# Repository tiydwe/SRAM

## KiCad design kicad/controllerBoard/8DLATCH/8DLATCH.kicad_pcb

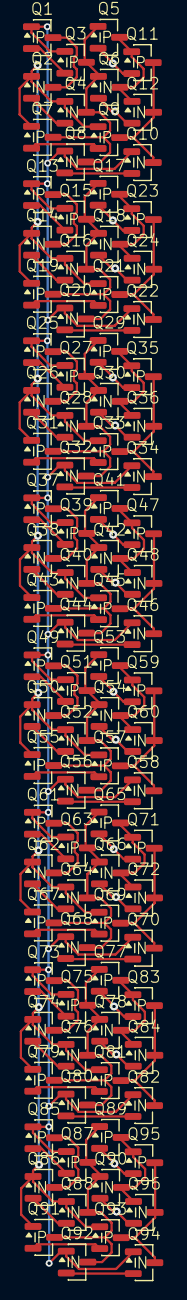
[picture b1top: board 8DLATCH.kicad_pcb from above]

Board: 2 copper layers, 96 parts (0 on the bottom side), 82 nets.

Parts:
Q1, Q3, Q5, Q7, Q9, Q11, Q13, Q15, Q17, Q19, Q21, Q23, Q25, Q27, Q29, Q31, Q33, Q35, Q37, Q39, Q41, Q43, Q45, Q47, Q49, Q51, Q53, Q55, Q57, Q59, Q61, Q63, Q65, Q67, Q69, Q71, Q73, Q75, Q77, Q79, Q81, Q83, Q85, Q87, Q89, Q91, Q93, Q95: Q_PMOS_GSD; SOT-23-P
Q2, Q4, Q6, Q8, Q10, Q12, Q14, Q16, Q18, Q20, Q22, Q24, Q26, Q28, Q30, Q32, Q34, Q36, Q38, Q40, Q42, Q44, Q46, Q48, Q50, Q52, Q54, Q56, Q58, Q60, Q62, Q64, Q66, Q68, Q70, Q72, Q74, Q76, Q78, Q80, Q82, Q84, Q86, Q88, Q90, Q92, Q94, Q96: Q_NMOS_GSD; SOT-23-N

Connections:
/D_{0}: Q1.3 (D), Q2.3 (D)
/D_{1}: Q13.3 (D), Q14.3 (D)
/D_{2}: Q25.3 (D), Q26.3 (D)
/D_{3}: Q37.3 (D), Q38.3 (D)
/D_{4}: Q49.3 (D), Q50.3 (D)
/D_{5}: Q61.3 (D), Q62.3 (D)
/D_{6}: Q73.3 (D), Q74.3 (D)
/D_{7}: Q85.3 (D), Q86.3 (D)
/EN: Q2.1 (G), Q4.1 (G), Q7.1 (G), Q9.1 (G), Q14.1 (G), Q16.1 (G), Q19.1 (G), Q21.1 (G), Q26.1 (G), Q28.1 (G), Q31.1 (G), Q33.1 (G), Q38.1 (G), Q40.1 (G), Q43.1 (G), Q45.1 (G), Q50.1 (G), Q52.1 (G), Q55.1 (G), Q57.1 (G), Q62.1 (G), Q64.1 (G), Q67.1 (G), Q69.1 (G), Q74.1 (G), Q76.1 (G), Q79.1 (G), Q81.1 (G), Q86.1 (G), Q88.1 (G), Q91.1 (G), Q93.1 (G)
/Q_{0}: Q9.3 (D), Q10.3 (D), Q11.3 (D), Q12.3 (D)
/Q_{1}: Q21.3 (D), Q22.3 (D), Q23.3 (D), Q24.3 (D)
/Q_{2}: Q33.3 (D), Q34.3 (D), Q35.3 (D), Q36.3 (D)
/Q_{3}: Q45.3 (D), Q46.3 (D), Q47.3 (D), Q48.3 (D)
/Q_{4}: Q57.3 (D), Q58.3 (D), Q59.3 (D), Q60.3 (D)
/Q_{5}: Q69.3 (D), Q70.3 (D), Q71.3 (D), Q72.3 (D)
/Q_{6}: Q81.3 (D), Q82.3 (D), Q83.3 (D), Q84.3 (D)
/Q_{7}: Q93.3 (D), Q94.3 (D), Q95.3 (D), Q96.3 (D)
/~EN: Q1.1 (G), Q3.1 (G), Q8.1 (G), Q10.1 (G), Q13.1 (G), Q15.1 (G), Q20.1 (G), Q22.1 (G), Q25.1 (G), Q27.1 (G), Q32.1 (G), Q34.1 (G), Q37.1 (G), Q39.1 (G), Q44.1 (G), Q46.1 (G), Q49.1 (G), Q51.1 (G), Q56.1 (G), Q58.1 (G), Q61.1 (G), Q63.1 (G), Q68.1 (G), Q70.1 (G), Q73.1 (G), Q75.1 (G), Q80.1 (G), Q82.1 (G), Q85.1 (G), Q87.1 (G), Q92.1 (G), Q94.1 (G)
/~Q_{0}: Q5.3 (D), Q6.3 (D), Q11.1 (G), Q12.1 (G)
/~Q_{1}: Q17.3 (D), Q18.3 (D), Q23.1 (G), Q24.1 (G)
/~Q_{2}: Q29.3 (D), Q30.3 (D), Q35.1 (G), Q36.1 (G)
/~Q_{3}: Q41.3 (D), Q42.3 (D), Q47.1 (G), Q48.1 (G)
/~Q_{4}: Q53.3 (D), Q54.3 (D), Q59.1 (G), Q60.1 (G)
/~Q_{5}: Q65.3 (D), Q66.3 (D), Q71.1 (G), Q72.1 (G)
/~Q_{6}: Q77.3 (D), Q78.3 (D), Q83.1 (G), Q84.1 (G)
/~Q_{7}: Q89.3 (D), Q90.3 (D), Q95.1 (G), Q96.1 (G)
unnamed: Q1.2 (S), Q3.2 (S)
unnamed: Q2.2 (S), Q4.2 (S)
unnamed: Q3.3 (D), Q4.3 (D), Q5.1 (G), Q6.1 (G), Q7.3 (D), Q8.3 (D)
unnamed: Q7.2 (S), Q9.2 (S)
unnamed: Q8.2 (S), Q10.2 (S)
unnamed: Q5.2 (S), Q11.2 (S)
unnamed: Q6.2 (S), Q12.2 (S)
unnamed: Q13.2 (S), Q15.2 (S)
unnamed: Q14.2 (S), Q16.2 (S)
unnamed: Q15.3 (D), Q16.3 (D), Q17.1 (G), Q18.1 (G), Q19.3 (D), Q20.3 (D)
unnamed: Q17.2 (S), Q23.2 (S)
unnamed: Q18.2 (S), Q24.2 (S)
unnamed: Q19.2 (S), Q21.2 (S)
unnamed: Q20.2 (S), Q22.2 (S)
unnamed: Q25.2 (S), Q27.2 (S)
unnamed: Q26.2 (S), Q28.2 (S)
unnamed: Q27.3 (D), Q28.3 (D), Q29.1 (G), Q30.1 (G), Q31.3 (D), Q32.3 (D)
unnamed: Q29.2 (S), Q35.2 (S)
unnamed: Q30.2 (S), Q36.2 (S)
unnamed: Q31.2 (S), Q33.2 (S)
unnamed: Q32.2 (S), Q34.2 (S)
unnamed: Q37.2 (S), Q39.2 (S)
unnamed: Q38.2 (S), Q40.2 (S)
unnamed: Q39.3 (D), Q40.3 (D), Q41.1 (G), Q42.1 (G), Q43.3 (D), Q44.3 (D)
unnamed: Q41.2 (S), Q47.2 (S)
unnamed: Q42.2 (S), Q48.2 (S)
unnamed: Q43.2 (S), Q45.2 (S)
unnamed: Q44.2 (S), Q46.2 (S)
unnamed: Q49.2 (S), Q51.2 (S)
unnamed: Q50.2 (S), Q52.2 (S)
unnamed: Q51.3 (D), Q52.3 (D), Q53.1 (G), Q54.1 (G), Q55.3 (D), Q56.3 (D)
unnamed: Q53.2 (S), Q59.2 (S)
unnamed: Q54.2 (S), Q60.2 (S)
unnamed: Q55.2 (S), Q57.2 (S)
unnamed: Q56.2 (S), Q58.2 (S)
unnamed: Q61.2 (S), Q63.2 (S)
unnamed: Q62.2 (S), Q64.2 (S)
unnamed: Q63.3 (D), Q64.3 (D), Q65.1 (G), Q66.1 (G), Q67.3 (D), Q68.3 (D)
unnamed: Q65.2 (S), Q71.2 (S)
unnamed: Q66.2 (S), Q72.2 (S)
unnamed: Q67.2 (S), Q69.2 (S)
unnamed: Q68.2 (S), Q70.2 (S)
unnamed: Q73.2 (S), Q75.2 (S)
unnamed: Q74.2 (S), Q76.2 (S)
unnamed: Q75.3 (D), Q76.3 (D), Q77.1 (G), Q78.1 (G), Q79.3 (D), Q80.3 (D)
unnamed: Q77.2 (S), Q83.2 (S)
unnamed: Q78.2 (S), Q84.2 (S)
unnamed: Q79.2 (S), Q81.2 (S)
unnamed: Q80.2 (S), Q82.2 (S)
unnamed: Q85.2 (S), Q87.2 (S)
unnamed: Q86.2 (S), Q88.2 (S)
unnamed: Q87.3 (D), Q88.3 (D), Q89.1 (G), Q90.1 (G), Q91.3 (D), Q92.3 (D)
unnamed: Q89.2 (S), Q95.2 (S)
unnamed: Q90.2 (S), Q96.2 (S)
unnamed: Q91.2 (S), Q93.2 (S)
unnamed: Q92.2 (S), Q94.2 (S)

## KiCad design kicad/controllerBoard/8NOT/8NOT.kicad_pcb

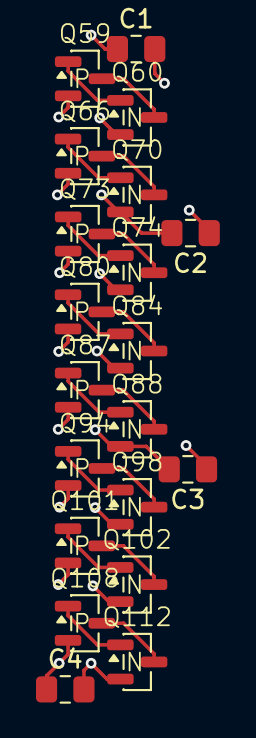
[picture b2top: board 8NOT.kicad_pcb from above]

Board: 2 copper layers, 20 parts (0 on the bottom side), 18 nets.

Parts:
C1, C2, C3, C4: C; C_0805_2012Metric_Pad1.18x1.45mm_HandSolder
Q59, Q66, Q73, Q80, Q87, Q94, Q101, Q108: Q_PMOS_GSD; SOT-23-P
Q60, Q70, Q74, Q84, Q88, Q98, Q102, Q112: Q_NMOS_GSD; SOT-23-N

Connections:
+5V: C1.1, C2.1, C3.1, C4.1, Q59.2 (S), Q66.2 (S), Q73.2 (S), Q80.2 (S), Q87.2 (S), Q94.2 (S), Q101.2 (S), Q108.2 (S)
/A_{0}: Q59.1 (G), Q60.1 (G)
/A_{1}: Q66.1 (G), Q70.1 (G)
/A_{2}: Q73.1 (G), Q74.1 (G)
/A_{3}: Q80.1 (G), Q84.1 (G)
/A_{4}: Q87.1 (G), Q88.1 (G)
/A_{5}: Q94.1 (G), Q98.1 (G)
/A_{6}: Q101.1 (G), Q102.1 (G)
/A_{7}: Q108.1 (G), Q112.1 (G)
/~A_{0}: Q59.3 (D), Q60.3 (D)
/~A_{1}: Q66.3 (D), Q70.3 (D)
/~A_{2}: Q73.3 (D), Q74.3 (D)
/~A_{3}: Q80.3 (D), Q84.3 (D)
/~A_{4}: Q87.3 (D), Q88.3 (D)
/~A_{5}: Q94.3 (D), Q98.3 (D)
/~A_{6}: Q101.3 (D), Q102.3 (D)
/~A_{7}: Q108.3 (D), Q112.3 (D)
GND: C1.2, C2.2, C3.2, C4.2, Q60.2 (S), Q70.2 (S), Q74.2 (S), Q84.2 (S), Q88.2 (S), Q98.2 (S), Q102.2 (S), Q112.2 (S)

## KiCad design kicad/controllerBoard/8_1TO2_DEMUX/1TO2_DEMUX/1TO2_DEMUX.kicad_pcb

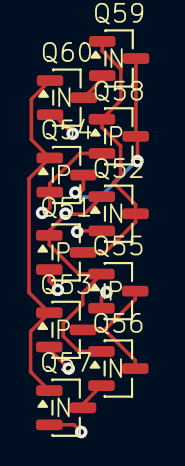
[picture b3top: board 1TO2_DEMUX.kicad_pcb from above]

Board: 2 copper layers, 10 parts (0 on the bottom side), 9 nets.

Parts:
Q51, Q53, Q54, Q55, Q58: Q_PMOS_GSD; SOT-23-P
Q52, Q56, Q57, Q59, Q60: Q_NMOS_GSD; SOT-23-N

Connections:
+5V: Q51.2 (S), Q53.2 (S), Q54.2 (S), Q55.2 (S), Q58.2 (S)
/Addr: Q51.1 (G), Q52.1 (G), Q55.1 (G), Q56.1 (G)
/D: Q53.1 (G), Q54.1 (G), Q57.1 (G), Q60.1 (G)
/~Y_{0}: Q54.3 (D), Q58.3 (D), Q59.3 (D)
/~Y_{1}: Q53.3 (D), Q55.3 (D), Q56.3 (D)
GND: Q52.2 (S), Q57.2 (S), Q60.2 (S)
unnamed: Q51.3 (D), Q52.3 (D), Q58.1 (G), Q59.1 (G)
unnamed: Q56.2 (S), Q57.3 (D)
unnamed: Q59.2 (S), Q60.3 (D)

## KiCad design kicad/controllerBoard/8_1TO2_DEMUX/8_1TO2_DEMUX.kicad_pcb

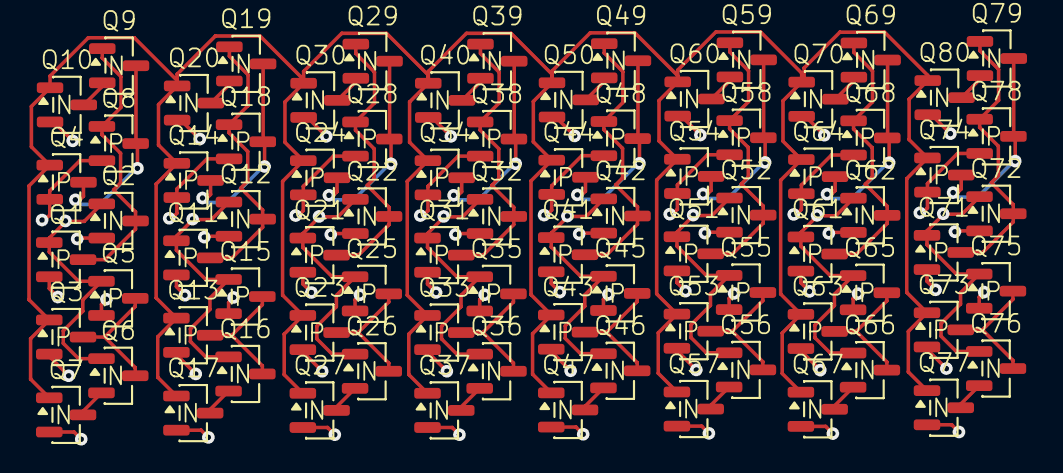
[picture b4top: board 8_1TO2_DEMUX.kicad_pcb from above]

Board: 2 copper layers, 80 parts (0 on the bottom side), 51 nets.

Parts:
Q1, Q3, Q4, Q5, Q8, Q11, Q13, Q14, Q15, Q18, Q21, Q23, Q24, Q25, Q28, Q31, Q33, Q34, Q35, Q38, Q41, Q43, Q44, Q45, Q48, Q51, Q53, Q54, Q55, Q58, Q61, Q63, Q64, Q65, Q68, Q71, Q73, Q74, Q75, Q78: Q_PMOS_GSD; SOT-23-P
Q2, Q6, Q7, Q9, Q10, Q12, Q16, Q17, Q19, Q20, Q22, Q26, Q27, Q29, Q30, Q32, Q36, Q37, Q39, Q40, Q42, Q46, Q47, Q49, Q50, Q52, Q56, Q57, Q59, Q60, Q62, Q66, Q67, Q69, Q70, Q72, Q76, Q77, Q79, Q80: Q_NMOS_GSD; SOT-23-N

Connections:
+5V: Q1.2 (S), Q3.2 (S), Q4.2 (S), Q5.2 (S), Q8.2 (S), Q11.2 (S), Q13.2 (S), Q14.2 (S), Q15.2 (S), Q18.2 (S), Q21.2 (S), Q23.2 (S), Q24.2 (S), Q25.2 (S), Q28.2 (S), Q31.2 (S), Q33.2 (S), Q34.2 (S), Q35.2 (S), Q38.2 (S), Q41.2 (S), Q43.2 (S), Q44.2 (S), Q45.2 (S), Q48.2 (S), Q51.2 (S), Q53.2 (S), Q54.2 (S), Q55.2 (S), Q58.2 (S), Q61.2 (S), Q63.2 (S), Q64.2 (S), Q65.2 (S), Q68.2 (S), Q71.2 (S), Q73.2 (S), Q74.2 (S), Q75.2 (S), Q78.2 (S)
/Addr_{0}: Q1.1 (G), Q2.1 (G), Q5.1 (G), Q6.1 (G)
/Addr_{1}: Q11.1 (G), Q12.1 (G), Q15.1 (G), Q16.1 (G)
/Addr_{2}: Q21.1 (G), Q22.1 (G), Q25.1 (G), Q26.1 (G)
/Addr_{3}: Q31.1 (G), Q32.1 (G), Q35.1 (G), Q36.1 (G)
/Addr_{4}: Q41.1 (G), Q42.1 (G), Q45.1 (G), Q46.1 (G)
/Addr_{5}: Q51.1 (G), Q52.1 (G), Q55.1 (G), Q56.1 (G)
/Addr_{6}: Q61.1 (G), Q62.1 (G), Q65.1 (G), Q66.1 (G)
/Addr_{7}: Q71.1 (G), Q72.1 (G), Q75.1 (G), Q76.1 (G)
/D: Q3.1 (G), Q4.1 (G), Q7.1 (G), Q10.1 (G), Q13.1 (G), Q14.1 (G), Q17.1 (G), Q20.1 (G), Q23.1 (G), Q24.1 (G), Q27.1 (G), Q30.1 (G), Q33.1 (G), Q34.1 (G), Q37.1 (G), Q40.1 (G), Q43.1 (G), Q44.1 (G), Q47.1 (G), Q50.1 (G), Q53.1 (G), Q54.1 (G), Q57.1 (G), Q60.1 (G), Q63.1 (G), Q64.1 (G), Q67.1 (G), Q70.1 (G), Q73.1 (G), Q74.1 (G), Q77.1 (G), Q80.1 (G)
/~Y_{0 0}: Q4.3 (D), Q8.3 (D), Q9.3 (D)
/~Y_{0 1}: Q14.3 (D), Q18.3 (D), Q19.3 (D)
/~Y_{0 2}: Q24.3 (D), Q28.3 (D), Q29.3 (D)
/~Y_{0 3}: Q34.3 (D), Q38.3 (D), Q39.3 (D)
/~Y_{0 4}: Q44.3 (D), Q48.3 (D), Q49.3 (D)
/~Y_{0 5}: Q54.3 (D), Q58.3 (D), Q59.3 (D)
/~Y_{0 6}: Q64.3 (D), Q68.3 (D), Q69.3 (D)
/~Y_{0 7}: Q74.3 (D), Q78.3 (D), Q79.3 (D)
/~Y_{1 0}: Q3.3 (D), Q5.3 (D), Q6.3 (D)
/~Y_{1 1}: Q13.3 (D), Q15.3 (D), Q16.3 (D)
/~Y_{1 2}: Q23.3 (D), Q25.3 (D), Q26.3 (D)
/~Y_{1 3}: Q33.3 (D), Q35.3 (D), Q36.3 (D)
/~Y_{1 4}: Q43.3 (D), Q45.3 (D), Q46.3 (D)
/~Y_{1 5}: Q53.3 (D), Q55.3 (D), Q56.3 (D)
/~Y_{1 6}: Q63.3 (D), Q65.3 (D), Q66.3 (D)
/~Y_{1 7}: Q73.3 (D), Q75.3 (D), Q76.3 (D)
GND: Q2.2 (S), Q7.2 (S), Q10.2 (S), Q12.2 (S), Q17.2 (S), Q20.2 (S), Q22.2 (S), Q27.2 (S), Q30.2 (S), Q32.2 (S), Q37.2 (S), Q40.2 (S), Q42.2 (S), Q47.2 (S), Q50.2 (S), Q52.2 (S), Q57.2 (S), Q60.2 (S), Q62.2 (S), Q67.2 (S), Q70.2 (S), Q72.2 (S), Q77.2 (S), Q80.2 (S)
unnamed: Q1.3 (D), Q2.3 (D), Q8.1 (G), Q9.1 (G)
unnamed: Q6.2 (S), Q7.3 (D)
unnamed: Q9.2 (S), Q10.3 (D)
unnamed: Q11.3 (D), Q12.3 (D), Q18.1 (G), Q19.1 (G)
unnamed: Q16.2 (S), Q17.3 (D)
unnamed: Q19.2 (S), Q20.3 (D)
unnamed: Q21.3 (D), Q22.3 (D), Q28.1 (G), Q29.1 (G)
unnamed: Q26.2 (S), Q27.3 (D)
unnamed: Q29.2 (S), Q30.3 (D)
unnamed: Q31.3 (D), Q32.3 (D), Q38.1 (G), Q39.1 (G)
unnamed: Q36.2 (S), Q37.3 (D)
unnamed: Q39.2 (S), Q40.3 (D)
unnamed: Q41.3 (D), Q42.3 (D), Q48.1 (G), Q49.1 (G)
unnamed: Q46.2 (S), Q47.3 (D)
unnamed: Q49.2 (S), Q50.3 (D)
unnamed: Q51.3 (D), Q52.3 (D), Q58.1 (G), Q59.1 (G)
unnamed: Q56.2 (S), Q57.3 (D)
unnamed: Q59.2 (S), Q60.3 (D)
unnamed: Q61.3 (D), Q62.3 (D), Q68.1 (G), Q69.1 (G)
unnamed: Q66.2 (S), Q67.3 (D)
unnamed: Q69.2 (S), Q70.3 (D)
unnamed: Q71.3 (D), Q72.3 (D), Q78.1 (G), Q79.1 (G)
unnamed: Q76.2 (S), Q77.3 (D)
unnamed: Q79.2 (S), Q80.3 (D)

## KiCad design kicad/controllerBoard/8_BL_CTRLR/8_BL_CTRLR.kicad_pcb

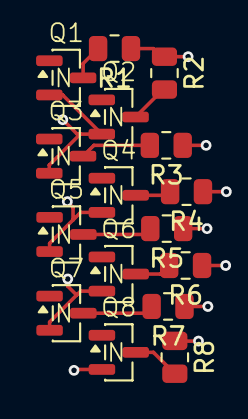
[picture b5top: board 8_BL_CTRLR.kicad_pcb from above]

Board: 2 copper layers, 16 parts (0 on the bottom side), 10 nets.

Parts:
Q1, Q2, Q3, Q4, Q5, Q6, Q7, Q8: Q_NMOS_GSD; SOT-23-N
R1, R2, R3, R4, R5, R6, R7, R8: 10kR; R_0805_2012Metric

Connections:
+5V: R1.1, R2.1, R3.1, R4.1, R5.1, R6.1, R7.1, R8.1
/BL_{0}: Q1.3 (D), R1.2
/BL_{1}: Q2.3 (D), R2.2
/BL_{2}: Q3.3 (D), R3.2
/BL_{3}: Q4.3 (D), R4.2
/BL_{4}: Q5.3 (D), R5.2
/BL_{5}: Q6.3 (D), R6.2
/BL_{6}: Q7.3 (D), R7.2
/BL_{7}: Q8.3 (D), R8.2
GND: Q1.2 (S), Q2.2 (S), Q3.2 (S), Q4.2 (S), Q5.2 (S), Q6.2 (S), Q7.2 (S), Q8.2 (S)

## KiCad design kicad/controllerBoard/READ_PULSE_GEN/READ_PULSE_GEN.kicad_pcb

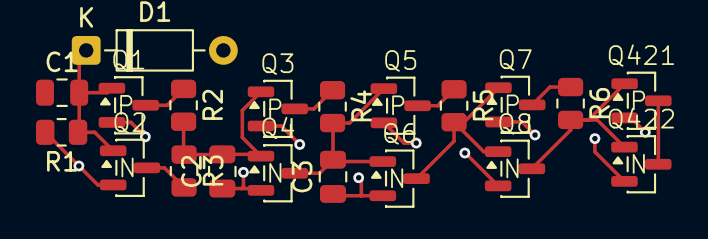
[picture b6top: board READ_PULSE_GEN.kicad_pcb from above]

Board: 2 copper layers, 20 parts (0 on the bottom side), 13 nets.

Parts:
C1, C2: 100nC; C_0805_2012Metric
C3: 4.7uC; C_0805_2012Metric
D1: 1N4148; D_DO-35_SOD27_P7.62mm_Horizontal
Q1, Q3, Q5, Q7, Q421: Q_PMOS_GSD; SOT-23-P
Q2, Q4, Q6, Q8, Q422: Q_NMOS_GSD; SOT-23-N
R1: 47kR; R_0805_2012Metric
R2, R5: 47R; R_0805_2012Metric
R3, R6: 4.7R; R_0805_2012Metric
R4: 4.7kR; R_0805_2012Metric

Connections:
+5V: Q1.2 (S), Q3.2 (S), Q5.2 (S), Q7.2 (S), Q421.2 (S)
/R_PULSE: Q8.3 (D), Q421.1 (G), Q422.1 (G), R6.2
/~R_PULSE: Q421.3 (D), Q422.3 (D)
GND: C2.1, C3.1, D1.2 (A), Q2.2 (S), Q4.2 (S), Q6.2 (S), Q8.2 (S), Q422.2 (S), R1.2
unnamed: C1.2, D1.1 (K), Q1.1 (G), Q2.1 (G), R1.1
unnamed: Q1.3 (D), R2.1
unnamed: Q2.3 (D), R3.2
unnamed: Q3.3 (D), R4.1
unnamed: C2.2, Q3.1 (G), Q4.1 (G), R2.2, R3.1
unnamed: C3.2, Q4.3 (D), Q5.1 (G), Q6.1 (G), R4.2
unnamed: Q5.3 (D), R5.1
unnamed: Q6.3 (D), Q7.1 (G), Q8.1 (G), R5.2
unnamed: Q7.3 (D), R6.1

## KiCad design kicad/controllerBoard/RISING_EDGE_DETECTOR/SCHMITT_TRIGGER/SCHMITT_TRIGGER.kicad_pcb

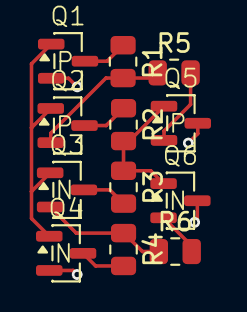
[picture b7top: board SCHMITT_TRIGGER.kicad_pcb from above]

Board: 2 copper layers, 12 parts (0 on the bottom side), 12 nets.

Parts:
Q1, Q2, Q5: Q_PMOS_GSD; SOT-23-P
Q3, Q4, Q6: Q_NMOS_GSD; SOT-23-N
R1, R2, R3, R4: 47R; R_0805_2012Metric
R5, R6: 10R; R_0805_2012Metric

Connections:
+5V: Q1.2 (S), Q6.3 (D)
/V_{in}: Q1.1 (G), Q2.1 (G), Q3.1 (G), Q4.1 (G)
/V_{out}: Q5.1 (G), Q6.1 (G), R2.2, R3.1
GND: Q4.2 (S), Q5.3 (D)
unnamed: Q1.3 (D), R1.1
unnamed: Q2.3 (D), R2.1
unnamed: Q2.2 (S), R1.2, R5.1
unnamed: Q3.3 (D), R3.2
unnamed: Q3.2 (S), R4.1, R6.1
unnamed: Q4.3 (D), R4.2
unnamed: Q5.2 (S), R5.2
unnamed: Q6.2 (S), R6.2
